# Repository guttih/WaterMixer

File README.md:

# Water Mixer

This project mixes water temperature from a 1/2" hot water pipe and a 1/2" cold water pipe out to a single 3/4" output 
water pipe.  A electrical valve controls the flow from the hot water pipe and another electrical valve controls the cold
water pipe.  A Temperature sensor is put into the 3/4" output water pipe to sense the current heat of the outgoing water.
Finally the third electrical valve is used to drain the hot tub. 

## Related links

- Project page (todo:)
- [Experiment page]
- [Hot-tub]
- Project [Development documents]

## Parts in project

- 1 x 12V Power supply
- 2 x [DC_STEPDOWN]
- 1 x [ESP32 Development Board]
- 1 x [DS18B20 Digital Temperature Sensor G3/4]
- 1 x [Logic level converter]
- 1 x [Dac MCP4728]
- 3 x [Proportional Valve Brass controllable with 0-5V]
- 1 x [LCD touch display]

## Api

Supported methods, requests and responses are described in the
[API methods]
## Wiring the project

### Schematic

```
                                                                                         +12V
                                                                                          ┬
  ┌───────────────────────────────────────────────────────────────────────────────────────┤
  │ ┌───────────────────┬──────────────────┬────────────────┬───────────────────────┬──┐  │
  │ │                   │                  │  ╔══════════╗  │  ╔═════════════╗      ┴  │  │
  │ │ ╔══════════════╗  │  ╔═════════════╗ │  ║ Pressure ║  │  ║     ADC     ║     GND │  │
  │ │ ║ POWER SOURCE ║  │  ║ DC_STEPDOWN ║ │  ║  Sensor  ║  │  ║   ADS1115   ║         │  │
  │ │ ║              ║  │  ║   -Vo(GND) -╟─┘  ║          ║  │  ║             ║         │  │
  │ │ ║              ║  │  ║   +Vo(+5V) -╟─┐  ║    Black-╟──┴──╢-G           ║         │  │
  │ │ ║              ║  │  ║             ║ │  ║    Green-╟─────╢-A0          ║         │  │
  │ └─╢-     GND    -╟──┴──╢-GND         ║ │  ║          ║     ╢-A1          ║         │  │
  └───╢-    +12V    -╟─────╢-VIN         ║ │  ║          ║     ╢-A2          ║         │  │
      ╚══════════════╝     ╚═════════════╝ │  ║          ║     ╢-A3          ║         │  │
                                           │  ║      Red-╟─┬───╢-V           ║         │  │
                      +5V                  │  ╚══════════╝ │ ┌─╢-CL       DA-╟─┐       │  │
                       ┬  ┌────────────────┴───────────────┘ │ ╚═════════════╝ │       │  │
                       └──┤                                  │                 │       │  │
                          │ ╔═══════════╗                    │ ╔═════════════╗ │       │  │
                          │ ║  -ESP32-  ║  ╔═════════════╗   │ ║     DAC     ║ │       │  │
                          │ ║           ║  ║ Logic Level ║   │ ║   MCP4728   ║ │       │  │
                          │ ║           ║  ║  converter  ║   │ ║             ║ │       │  │
                          └─╢-VIN   G14-╟──╢-LV3     HV3-╟───┴─╢-CL          ║ │       │  │
                            ║       G13-╟──╢-LV4     HV4-╟─────╢-DA───────DA-╟─┘       │  │
 +3V3   ╔═══════════╗       ║           ║  ║             ║     ║             ║         │  │
  ┬     ║  Resistor ║       ║           ║  ║             ║ +5V ║           D-╟──────┐  │  │
┌─┴─────╢-  4.7kΩ  -╟─────┬─╢-G25       ║  ║             ║  ┬  ║           C-╟      │  │  │
│       ╚═══════════╝     │ ║       3V3-╟──╢-LV       HV-╟──┴──╢-V         B-╟────┐ │  │  │
│       ╔═══════════╗     │ ║       GND-╟──╢-GND     GND-╟──┬──╢-G         A-╟──┐ │ │  │  │
│       ║  DS18B20  ║     │ ║           ║  ╚═════════════╝  ┴  ╚═════════════╝  │ │ │  │  │
│       ║   Temp    ║     │ ║           ║                  GND                  │ │ │  │  │
│       ║           ║     │ ║           ║                                       │ │ │  │  │
│       ║    SIGNAL-╟─(YE)┘ ║           ║   ┌───────────────────────────────────┘ │ │  │  │
├──(RD)─╢-VCC       ║       ║           ║   │    ┌────────────────────────────────┘ │  │  │
│ ┌(BL)─╢-GND       ║       ║           ║   │    │    ┌─────────────────────────────┘  │  │
│ │     ╚═══════════╝       ║  -ESP32-  ║   │    │    │        ╔════════════╗          │  │
│ │                         ║           ║   │    │    │        ║   Valve D  ║          │  │
│ │                         ║           ║   │    │    │        ║        GND-╟─(BL)─────┤  │
│ │                         ║           ║   │    │    └───(GR)─╢-LIN    ERR-╟─(YE)─    ┴  │
│ │                         ║           ║   │    │             ║    PWM Out-╟─(WT)─   GND │
│ ├─────────────────────┬───╢-GND       ║   │    │             ║        VCC-╟─(RD)────────┤
│ │  ╔══════════════╗   │   ║           ║   │    │             ╚════════════╝             │
│ │  ║   LCD TOUCH  ║   │   ║           ║   │    │             ╔════════════╗             │
│ │  ║    DISPLAY   ║   │   ║           ║   │    │             ║   Valve C  ║             │
│ │  ║              ║   │   ║           ║   │    │             ║        GND-╟─(BL)─────┐  │
│ │  ║          GND-╟───┘   ║  -ESP32-  ║   │    └─────── (GR)─╢-LIN    ERR-╟─(YE)─    ┴  │
│ │  ║      SD_MOSI-╟─┐     ║           ║   │                  ║    PWM Out-╟─(WT)─   GND │
│ │  ║         MOSI-╟─┼───┐ ║           ║   │                  ║        VCC-╟─(RD)────────┤
│ │  ║        T_DIN-╟─┘   │ ║           ║   │                  ╚════════════╝             │
│ │  ║       SD_SCK-╟─┐   │ ║           ║   │                  ╔════════════╗             │
│ │  ║          SCK-╟─┼─┐ │ ║           ║   │                  ║   Valve H  ║             │
│ │  ║        T_CLK-╟─┘ │ └─╢-G23       ║   │                  ║        GND-╟─(BL)─────┐  │
│ │  ║         T_DO-╟─┐ └───╢-G18       ║   └─────────────(GR)─╢-LIN    ERR-╟─(YE)─    ┴  │
│ │  ║      SD_MISO-╟─┴─────╢-G19       ║                      ║    PWM Out-╟─(WT)─   GND │
│ │  ║           CS-╟───────╢-G15       ║                      ║        VCC-╟─(RD)────────┤
│ │  ║        RESET-╟───────╢-G4        ║                      ╚════════════╝             │
│ │  ║           DC-╟───────╢-G2        ║  ┌─────────────────────────┐                    │
│ │  ║        SD_CS-╟───────╢-G5        ║  │        ╔═════════════╗  │                    │
│ │  ║         T_CS-╟───────╢-G21       ║  │        ║ DC_STEPDOWN ║  │                    │
│ │  ║              ║       ║  -ESP32-  ║  │        ║             ║  │                    │
│ │  ║          VCC-╟─┐     ╚═══════════╝  │  ┌─────╢- -Vo( GND) -╟  │  ┌────┐            │
│ │  ║          LED-╟─┴────────────────────┘  │  ┌──╢- +Vo(+3V3) -╟──┘  │    ┴            │
│ │  ╚══════════════╝                         │  │  ║         GND-╟─────┘   GND           │
│ └───────────────────────────────────────────┘  │  ║         VIN-╟───────────────────────┘
└────────────────────────────────────────────────┘  ╚═════════════╝                         
```
Legend

- <span style="background: black; color: white">(BL) = Black wire (-Ground)</span>
- <span style="background: red; color: white">(RD) = Red wire (+VCC)</span>
- <span style="background: yellow; color: black">(YE) = Yellow wire</span>
- <span style="background: green; color: white">(GR) = Green wire (voltage signal)</span>
- <span style="background: white; color: black">(WT) = White wire</span>
- GND    : Ground.
- ` ┴` 
- `GND`  : Ground.  When there is no room to connect the GND on the drawing, this notation is used.  Note, *all grounds are connected together*.
- VIN    : 5V pin on the esp32 pin.
- G34    : Esp32 GPIO 34 pin which is used to measure voltage coming from pressure sensor.
- G25    : Esp32 GPIO 25 pin which is used to communicate with the temperature sensor.
- G12    : Esp32 GPIO 12 pin which is used control the hot water valve.
- G14    : Esp32 GPIO 14 pin which is used control the cold water valve.
- G32    : Esp32 GPIO 32 pin which is used control the drain water valve.
- G##    : Other esp32 pins used to control the touch display and read and write to a sd card.
- Valve H: Hot valve
- Valve C: Cold valve
- Valve D: Drain valve

## Software development

The software for this project was developed using [PlatformIO].

### Tests

There are two kinds of tests in this project, *integration tests* and *unit tests*.

__Integration tests__:
*integration tests* are located in the `./test` directory.

On windows 10, best would be if you would add this location to your PATH system environment variable __C:\Users\your_user_name\.platformio\penv\Scripts__ to get access to the pio.exe application.
C:\Users\gudjons\.platformio\penv\Scripts
Then you can run the tests with this command `pio test`

[DC_STEPDOWN]:https://www.aliexpress.com/item/32531438467.html?spm=a2g0s.9042311.0.0.27424c4dWJSXmG
[ESP32 Development Board]:https://www.aliexpress.com/item/32801621054.html?spm=a2g0s.9042311.0.0.27424c4dOggB1n
[DS18B20 Digital Temperature Sensor G3/4]:https://www.aliexpress.com/item/32881183992.html?spm=a2g0s.12269583.0.0.43c751fcxDyDbt
[Logic level converter]:https://www.aliexpress.com/item/32308653416.html?spm=a2g0s.9042311.0.0.27424c4dy510IB
[Dac MCP4728]:https://www.aliexpress.com/item/32975252305.html?spm=a2g0s.12269583.0.0.142b3d73bl1KXq
[Proportional Valve Brass controllable with 0-5V]:https://www.aliexpress.com/item/33037988030.html?spm=a2g0s.12269583.0.0.49d04a42eL9zNl
[Experiment page]: https://guttih.com/list/project-hottub-temp
[Hot-tub]:http://192.168.1.79/list/project-hottub
[cmake]:https://cmake.org/download/#latest
[PlatformIO]:https://platformio.org/
[Development documents]: docs/development/development.md
[LCD touch display]: https://www.aliexpress.com/item/4000030399357.html?spm=a2g0s.12269583.0.0.687d6973QvjfAl
[API methods]: docs/apiMethods.adoc

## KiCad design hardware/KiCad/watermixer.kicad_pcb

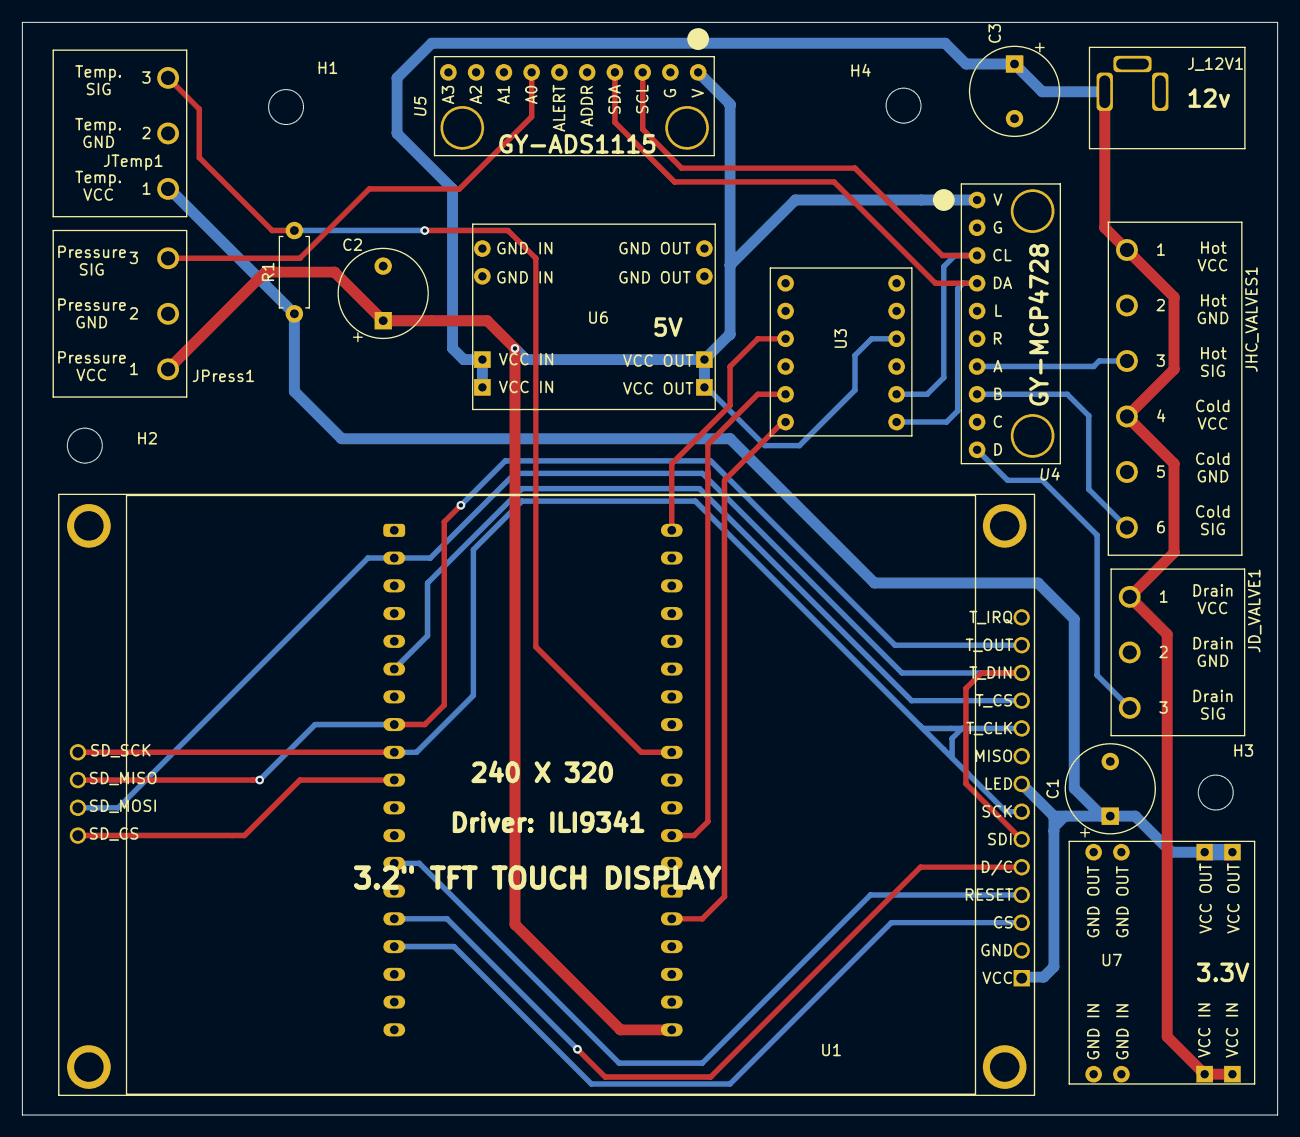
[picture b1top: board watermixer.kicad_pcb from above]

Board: 2 copper layers, 114.9 x 100.0 mm, 20 parts (1 on the bottom side), 22 nets.

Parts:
C1, C2, C3: 470uF; CP_Radial_Tantal_D8.0mm_P5.00mm
H1, H2, H3, H4: MountingHole; MountingHole_3.2mm_M3
JD_VALVE1: 01x03; Screw_Termianl_01x03
JHC_VALVES1: 01x06; Screw_Termianl_01x06
JPress1: Pressure sensor; Screw_Termianl_01x03
JTemp1: Temperature sensor; Screw_Termianl_01x03
J_12V1: Barrel_Jack
R1: 4.7k; R_Axial_DIN0207_L6.3mm_D2.5mm_P7.62mm_Horizontal
U1: CR2013-MI2120-touch; CR2013-MI2120_touch
U2: ESP32-DevKitC
U3: LLC_4CH
U4: MCP4728; MCP4728_module
U5: ADS1115; ADS1115_module
U6, U7: SD_BUCK3A

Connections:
+3V3: C1.1, JTemp1.1, R1.1, U1.1, U1.8, U7.2, U7.6
+5V: C2.1, JPress1.1, U2.19, U3.2, U4.1, U5.1, U6.2, U6.6
+12V: C3.1, JD_VALVE1.1, JHC_VALVES1.1, JHC_VALVES1.4, J_12V1.1, U6.1, U6.5, U7.1, U7.5
/SIGP: JPress1.3, U5.6
/SIGT: JTemp1.3, R1.2, U2.9
GND: C1.2, C2.2, C3.2, JD_VALVE1.2, JHC_VALVES1.2, JHC_VALVES1.5, JPress1.2, JTemp1.2, J_12V1.2, J_12V1.3, U1.2, U2.14, U2.32, U2.38, U3.3, U4.10, U5.10, U6.3, U6.4, U6.7, U6.8, U7.3, U7.4, U7.7, U7.8
unnamed: JD_VALVE1.3, U4.9
unnamed: JHC_VALVES1.3, U4.6
unnamed: JHC_VALVES1.6, U4.7
unnamed: U1.3, U2.23
unnamed: U1.4, U2.26
unnamed: U1.5, U2.24
unnamed: U1.10, U2.29
unnamed: U1.6, U1.11, U1.16, U2.37
unnamed: U1.12, U1.17, U2.31
unnamed: U1.7, U1.13, U1.14, U2.30
unnamed: U1.15, U2.33
unnamed: U2.1, U3.1
unnamed: U2.12, U3.8
unnamed: U2.15, U3.10
unnamed: U3.9, U4.2, U5.2
unnamed: U3.11, U4.3, U5.3

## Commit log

2021-06-27 adding readme.md
2021-06-27 pretting readme wiring
2021-06-27 readme
2021-06-27 adding PWM to voltatem test program
2021-06-27 fix pwm link
2021-06-28 adding test folders
2021-06-28 adding tests
2021-06-29 valve is functional
2021-06-29 adding serial_valve.cpp example
2021-06-29 adding serial.print to serial_valve.cpp example
2021-06-29 serial_value.cpp example
2021-06-29 simplyfing serial_valve.cpp
2021-06-29 adding serial_valves.cpp example
2021-06-29 example serial_valves.cpp type
2021-06-29 temperature sensor, adding DallasTemperature and OneWire
2021-06-30 started on watermixer, and fixed double macthing in tests
2021-07-01 adding header to tests
2021-07-01 what to do next
2021-07-03 adding flowmocker
2021-07-03 Fixing setChangeStepInterval in FlowMocker
2021-07-14 Working on Product Requirements Document
2021-07-14 adding System requirements
2021-07-14 adding UserStories.md
2021-07-14 adding valve status to user story
2021-07-15 adding story "change the PID values"
2021-07-16 Adding pressure sensor example sketch
2021-07-16 ajusting comments for read_pressure.cpp
2021-07-18 Adding plumming diagram
2021-07-19 adding hardware.md
2021-07-19 fix link in readme
2021-07-19 rename dir 1
2021-07-19 rename dir 2
2021-07-19 fix systemRequirements.md links
2021-07-19 fix ssystemrequirements link
2021-07-19 fixing link 3v3_power_supply
2021-07-19 development.md
2021-07-19 adding story dim backlight
2021-07-20 moving pressure sensor reading down to 1.1
2021-07-28 changeing pipe diagram
2021-07-29 Changing the pipe drawing a little
2021-07-31 can connect to VoffCon and display on GUI
2021-07-31 setting up
2021-07-31 gitignore
2021-07-31 asdf
2021-07-31 ignoring config.h
2021-08-03 can manually control valves hot, cold, drain
2021-08-04 Redrawed the schematic showing current pins and connections
2021-08-04 replacing HLK-PM01 and HLK-PM03 with DC_STEPDOWN
2021-08-04 removing extra spaces from schematic
2021-08-04 shorting the schematic
2021-08-04 Merging the two schematics
2021-08-04 moving 3v3 stepdown
2021-08-04 moving DC_STEPDOWN up a little
2021-08-04 schematic small fix
2021-08-05 Making temperature reading non-blocking and pressure reading return average of 30 samples
2021-08-06 can scan system and fill from desired temperature
2021-08-07 adding upload program wirelessly
2021-08-15 using setTextAlign instead of setDatum and writing information in md on how to upload program via wifi
2021-08-15 adding remote fill, stop and drain user stories
2021-08-15 adding fill, drain stop and flow commands to /custom route
2021-08-15 can fill remotly without specifyig temperature
2021-08-15 can send commands
2021-08-19 Desired temp now changes on start page when new value comes from web
2021-09-11 replacing ledcAnalogWrite with setChannelValue from Adafruit_MCP4728 library and removing unnessacery tests
2021-09-11 Removing PWM to Voltage converter and adding DAC to documentation
2021-09-11 adding dac to documentation
2021-09-12 set upload port ti ip address
2021-09-12 BC337 is not needed, we can use pwm from the eps32 pin
2021-09-12 BC337 is not needed
2021-09-14 Started designing PCB in KiCad
2021-09-14 All Compoents created and added to Schematic
2021-09-15 Done connecting all parts on the schema
2021-09-15 got a error free schematic
2021-09-15 power fixes before running starting PCB editor
2021-09-15 Pcb parts placed, but no traces yet
2021-09-16 Connected all on PCB except GND
2021-09-16 before grounding
2021-09-16 added GND fill zones on top and bottom layers
2021-09-16 Exported the production files
2021-10-02 starting to add an ADC
2021-10-02 added ADS1115 to pcb and ordered 5 pcbs with current production
2021-10-03 Adding SDS1115 to Schematic in README.md
2021-10-03 reading pressure value from ADS1115
2021-10-03 DallasTemperature.h includes OneWire no need to do it twice
2021-10-16 adding mesurements for 3d printing
2021-10-16 adding width
2021-12-12 Adding hostname= "WaterMixer"
2023-02-19 udating hostname and reconnect on wifi lost
2023-05-18 values will be logged to voffcon and can be queried with /pins
2023-05-20 working on voffcon control and card
2023-05-20 Saving
2023-05-20 adding update command to voffcon and device and calculating waterlevel
2023-05-21 blob animation active
2023-05-21 time left text below blob
2023-05-21 adding GET /samples and /samples/csv
2023-05-21 adding api metods documentation and a get methods to download samples /samples
2023-05-21 updating apiMethods document - POST /custom
2023-05-21 documentation for POST /custom
2023-05-21 update get object for monitors
2023-05-22 help apiMethods.adoc - updating post and delete objects
2023-05-23 little api help update
2023-05-27 Adding Brett's PID Library
2023-05-28 Adding PID controller test, but it is still inactive. Also corrected some spelling errors
2023-05-28 Adding a custom test, arduino independent (using cmake)
2023-05-28 customTest README.md update
2023-05-28 adding nowMs to main of glibTester
2023-05-29 Adding a hello world testSimulator which makes no sense
2023-06-01 adding build to .gitignore
2023-06-04 formatting

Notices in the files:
hardware/KiCad/watermixer.kicad_pcb:
Licence: CC BY 4.0
